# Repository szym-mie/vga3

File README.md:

# VGA FPGA Video Card implementation

## Display

This module works in standard VGA mode of 640x480 at 60Hz monitor refresh rate. The picture itself was scaled down to 160x120, but can be reverted to be true 640x480.

Full specification:

```
pixel clock: 25MHz
-0.7% deviation from ideal 25.175MHz

pixel mode: RGB222 6bpp
max analog color output voltage: 0.6V
sync signal level: 3.3V
```

## Hardware

### CAUTION

SPI connection requires 3.3V voltage level for safe operation

---

Apart from standard VGA connector, there is a SPI connection:

```
[  GND ]--(1)
< CSEL ]--(2)
< MOSI ]--(3)
< SCLK ]--(4)
```

FPGA:
```
MIMAS SPARTAN6 MODULE
```

Memory:
```
IS61LV5128AL 512K x 8 HIGH-SPEED CMOS STATIC RAM
access max time: 10, 12ns
full read/write max time: <20ns 
```

## Video memory

The video memory access is handled by module `vmmu.v`, which coordinates read access by VGA display unit and write access by SPI interface.

The basic working mechanism is the use of FIFOs to queue request addresses and read/write data.
Then the module can alternate between executing read and write requests, or if only one source has an active request, only that source is being processed.

The usage of FIFOs also make the system memory independent of other video circutry in terms of clock domains, further making the design more flexible.

## Schematics

As of recent update I've recovered KiCAD schematics and PCB design that contained system memory, SPI input and VGA connector. Those can be found under `kicad` directory.

## Modules

- spi.v - 8-bit SPI sampling receiver
- vbuf.v - video output buffer, also able to read 3 packed bytes to 4 pixels
- vcmd2v.v - video command processor, interacts with received data from SPI
- vctl.v - video output counter unit, sends signals related to video signal blanking and issues pixel read requests
- vsig.v - generates HSync and VSync VGA signals, along with global blank signal
- fifo.v - First-In-First-Out, asynchronous queue, with Full/Empty signals
- seqfifo.v - Generates sequences of addresses from staring address behaving as regular FIFO
- vmmu.v - video memory managment unit, time-slots reads and writes, controls memory chip
- vga.v - top-level module

## Bugs

#### 160x120 picture resolution (unresolved)

This was a hardware fault that prevented me from using a full 640x480. It turned out that one of the address lines was busted and it basically could corrupt the whole lower half of the screen. In theory I such issue could be remedied remap that region to an area that didn't use that address line.

#### PCB design mistake (fixed)

Due to confusing and just plain wrong schematic of pin headers that was published on Mimas site, one of data lines ended up connected to chip ground. This required an ad hoc jumper wire to be connected to a new location on a pin header, and a previous trace to be cut.

#### Dummy byte write needed after cursor move (unresolved)

An annoying issue, this results from tricky synchronization problems when the command to change cursor location is received. I was unable to fix it due to time constraint, instead a software workadround was devised, by writing a dummy byte just after `vga_set_xy`. This solution is not perfect and can cause flickering, depending on SPI data rate.

## Example driver code

A simple test driver code for ATMega88 (and its derivitives) can be found in `test_driver` directory. This test includes a simple color pallette pattern and animated analog speedometer.

The other example is included as a submodule [`vga_snake`](https://github.com/szym-mie/vga_snake) and it's a snake game demo written in C.

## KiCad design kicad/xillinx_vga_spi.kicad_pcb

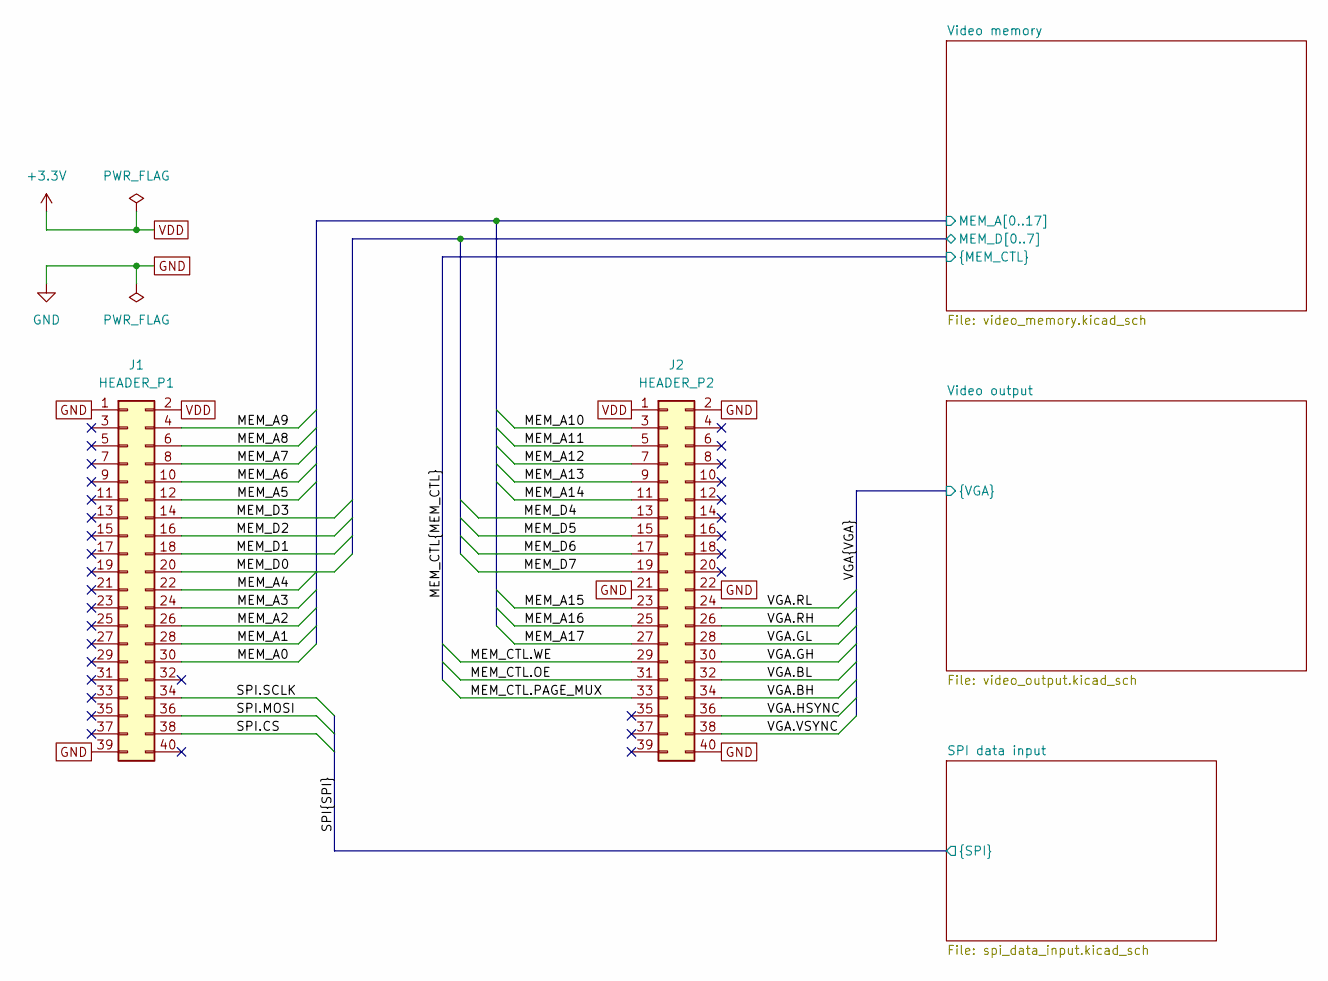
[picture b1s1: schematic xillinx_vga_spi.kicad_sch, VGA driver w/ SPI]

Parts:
J1: HEADER_P1; PinHeader_2x20_P2.54mm_Vertical
J2: HEADER_P2; PinHeader_2x20_P2.54mm_Vertical

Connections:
/MEM_CTL.OE: J2.31; also elsewhere on the board
/MEM_CTL.PAGE_MUX: J2.33; also elsewhere on the board
/MEM_CTL.WE: J2.29; also elsewhere on the board
/SPI.CS: J1.38; also elsewhere on the board
/SPI.MOSI: J1.36; also elsewhere on the board
/SPI.SCLK: J1.34; also elsewhere on the board
/VGA.BH: J2.34; also elsewhere on the board
/VGA.BL: J2.32; also elsewhere on the board
/VGA.GH: J2.30; also elsewhere on the board
/VGA.GL: J2.28; also elsewhere on the board
/VGA.HSYNC: J2.36; also elsewhere on the board
/VGA.RH: J2.26; also elsewhere on the board
/VGA.RL: J2.24; also elsewhere on the board
/VGA.VSYNC: J2.38; also elsewhere on the board
/Video memory/MEM_A0: J1.30; also elsewhere on the board
/Video memory/MEM_A1: J1.28; also elsewhere on the board
/Video memory/MEM_A2: J1.26; also elsewhere on the board
/Video memory/MEM_A3: J1.24; also elsewhere on the board
/Video memory/MEM_A4: J1.22; also elsewhere on the board
/Video memory/MEM_A5: J1.12; also elsewhere on the board
/Video memory/MEM_A6: J1.10; also elsewhere on the board
/Video memory/MEM_A7: J1.8; also elsewhere on the board
/Video memory/MEM_A8: J1.6; also elsewhere on the board
/Video memory/MEM_A9: J1.4; also elsewhere on the board
/Video memory/MEM_A10: J2.3; also elsewhere on the board
/Video memory/MEM_A11: J2.5; also elsewhere on the board
/Video memory/MEM_A12: J2.7; also elsewhere on the board
/Video memory/MEM_A13: J2.9; also elsewhere on the board
/Video memory/MEM_A14: J2.11; also elsewhere on the board
/Video memory/MEM_A15: J2.23; also elsewhere on the board
/Video memory/MEM_A16: J2.25; also elsewhere on the board
/Video memory/MEM_A17: J2.27; also elsewhere on the board
/Video memory/MEM_D0: J1.20; also elsewhere on the board
/Video memory/MEM_D1: J1.18; also elsewhere on the board
/Video memory/MEM_D2: J1.16; also elsewhere on the board
/Video memory/MEM_D3: J1.14; also elsewhere on the board
/Video memory/MEM_D4: J2.13; also elsewhere on the board
/Video memory/MEM_D5: J2.15; also elsewhere on the board
/Video memory/MEM_D6: J2.17; also elsewhere on the board
/Video memory/MEM_D7: J2.19; also elsewhere on the board
GND: J1.1, J1.39, J2.2, J2.21, J2.22, J2.40; also elsewhere on the board
VDD: J1.2, J2.1; also elsewhere on the board

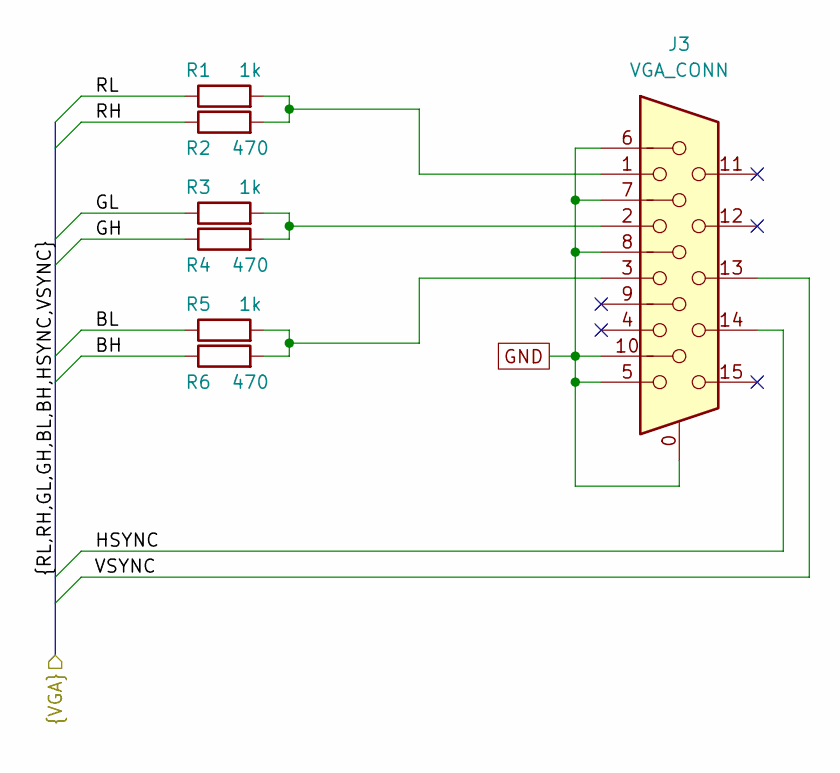
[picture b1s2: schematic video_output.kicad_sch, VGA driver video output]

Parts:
J3: VGA_CONN; L77HDE15SD1CH4FVGA
R1, R3, R5: 1k; R_0805_2012Metric_Pad1.20x1.40mm_HandSolder
R2, R4, R6: 470; R_0805_2012Metric_Pad1.20x1.40mm_HandSolder

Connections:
/VGA.BH: R6.1; also elsewhere on the board
/VGA.BL: R5.1; also elsewhere on the board
/VGA.GH: R4.1; also elsewhere on the board
/VGA.GL: R3.1; also elsewhere on the board
/VGA.HSYNC: J3.14; also elsewhere on the board
/VGA.RH: R2.1; also elsewhere on the board
/VGA.RL: R1.1; also elsewhere on the board
/VGA.VSYNC: J3.13; also elsewhere on the board
GND: J3.0, J3.5, J3.6, J3.7, J3.8, J3.10; also elsewhere on the board
unnamed: J3.1, R1.2, R2.2
unnamed: J3.2, R3.2, R4.2
unnamed: J3.3, R5.2, R6.2

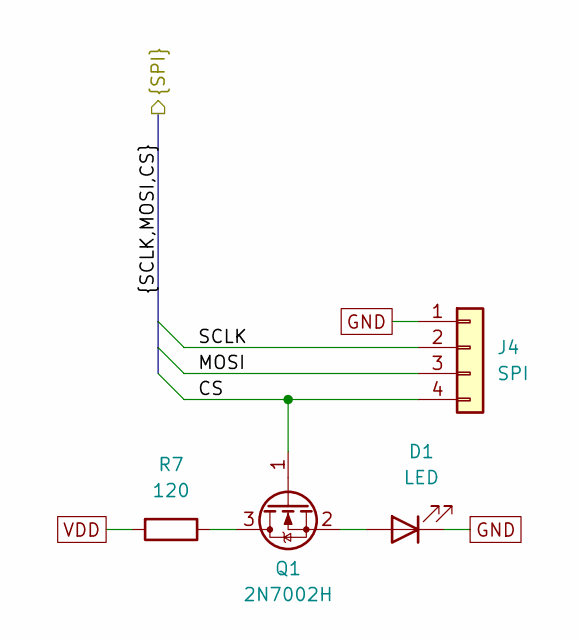
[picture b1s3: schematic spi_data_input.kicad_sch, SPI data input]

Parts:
D1: LED; LED_1206_3216Metric_Pad1.42x1.75mm_HandSolder
J4: SPI; PinSocket_1x04_P2.54mm_Horizontal
Q1: 2N7002H; SOT-23
R7: 120; R_0805_2012Metric_Pad1.20x1.40mm_HandSolder

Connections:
/SPI.CS: J4.4, Q1.1 (G); also elsewhere on the board
/SPI.MOSI: J4.3; also elsewhere on the board
/SPI.SCLK: J4.2; also elsewhere on the board
GND: D1.1 (K), J4.1; also elsewhere on the board
unnamed: D1.2 (A), Q1.2 (S)
unnamed: Q1.3 (D), R7.1
VDD: R7.2; also elsewhere on the board

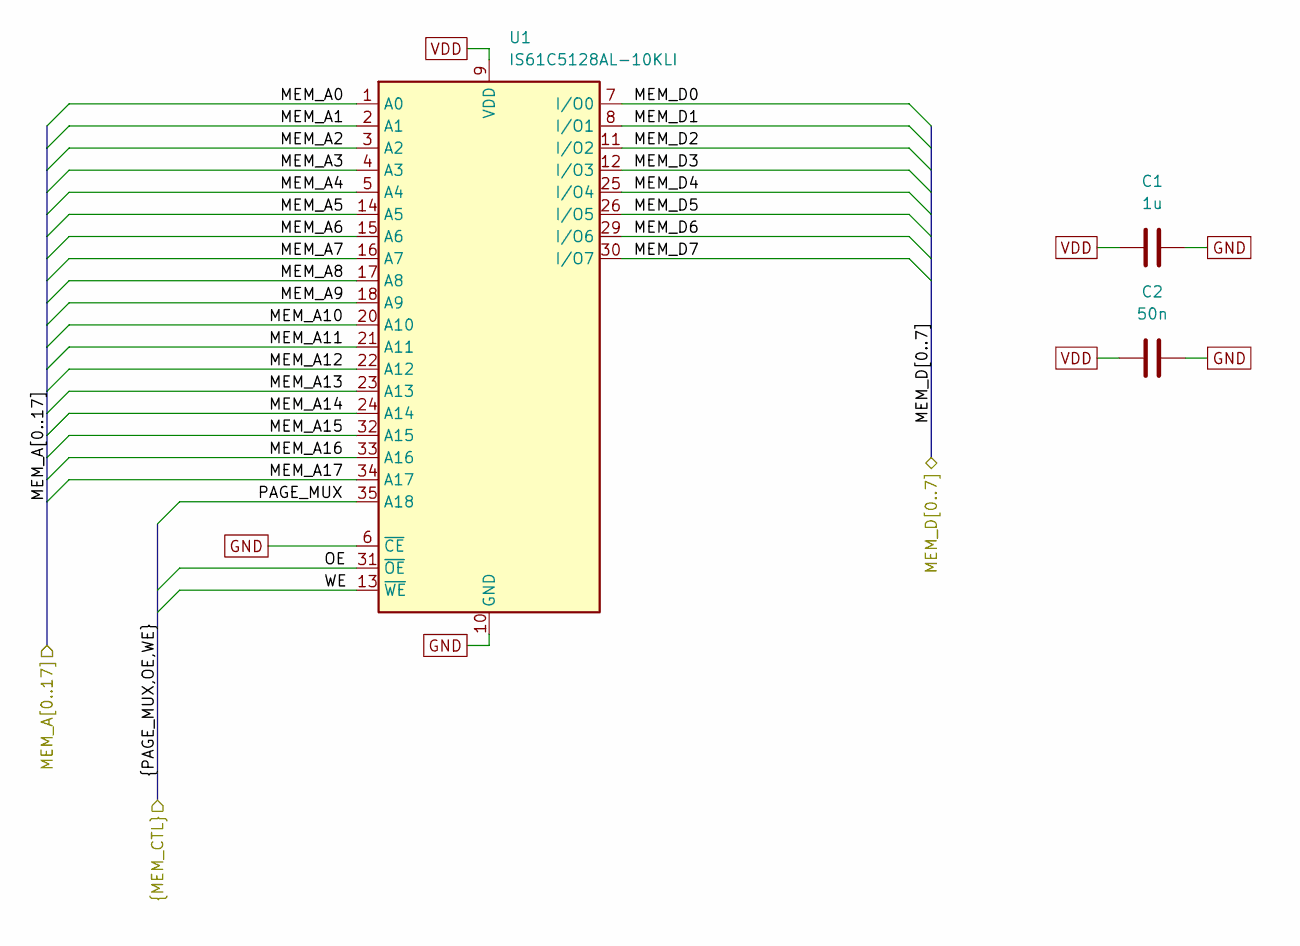
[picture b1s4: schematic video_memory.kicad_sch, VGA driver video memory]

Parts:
C1: 1u; C_0805_2012Metric_Pad1.18x1.45mm_HandSolder
C2: 50n; C_0805_2012Metric_Pad1.18x1.45mm_HandSolder
U1: IS61C5128AL-10KLI; SOJ-36_10.16x23.49mm_P1.27mm

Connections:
/MEM_CTL.OE: U1.31 (~OE); also elsewhere on the board
/MEM_CTL.PAGE_MUX: U1.35 (A18); also elsewhere on the board
/MEM_CTL.WE: U1.13 (~WE); also elsewhere on the board
/Video memory/MEM_A0: U1.1 (A0); also elsewhere on the board
/Video memory/MEM_A1: U1.2 (A1); also elsewhere on the board
/Video memory/MEM_A2: U1.3 (A2); also elsewhere on the board
/Video memory/MEM_A3: U1.4 (A3); also elsewhere on the board
/Video memory/MEM_A4: U1.5 (A4); also elsewhere on the board
/Video memory/MEM_A5: U1.14 (A5); also elsewhere on the board
/Video memory/MEM_A6: U1.15 (A6); also elsewhere on the board
/Video memory/MEM_A7: U1.16 (A7); also elsewhere on the board
/Video memory/MEM_A8: U1.17 (A8); also elsewhere on the board
/Video memory/MEM_A9: U1.18 (A9); also elsewhere on the board
/Video memory/MEM_A10: U1.20 (A10); also elsewhere on the board
/Video memory/MEM_A11: U1.21 (A11); also elsewhere on the board
/Video memory/MEM_A12: U1.22 (A12); also elsewhere on the board
/Video memory/MEM_A13: U1.23 (A13); also elsewhere on the board
/Video memory/MEM_A14: U1.24 (A14); also elsewhere on the board
/Video memory/MEM_A15: U1.32 (A15); also elsewhere on the board
/Video memory/MEM_A16: U1.33 (A16); also elsewhere on the board
/Video memory/MEM_A17: U1.34 (A17); also elsewhere on the board
/Video memory/MEM_D0: U1.7 (I/O0); also elsewhere on the board
/Video memory/MEM_D1: U1.8 (I/O1); also elsewhere on the board
/Video memory/MEM_D2: U1.11 (I/O2); also elsewhere on the board
/Video memory/MEM_D3: U1.12 (I/O3); also elsewhere on the board
/Video memory/MEM_D4: U1.25 (I/O4); also elsewhere on the board
/Video memory/MEM_D5: U1.26 (I/O5); also elsewhere on the board
/Video memory/MEM_D6: U1.29 (I/O6); also elsewhere on the board
/Video memory/MEM_D7: U1.30 (I/O7); also elsewhere on the board
GND: C1.2, C2.2, U1.6 (~CE), U1.10 (GND), U1.28 (GND); also elsewhere on the board
VDD: C1.1, C2.1, U1.9 (VDD), U1.27 (VDD); also elsewhere on the board

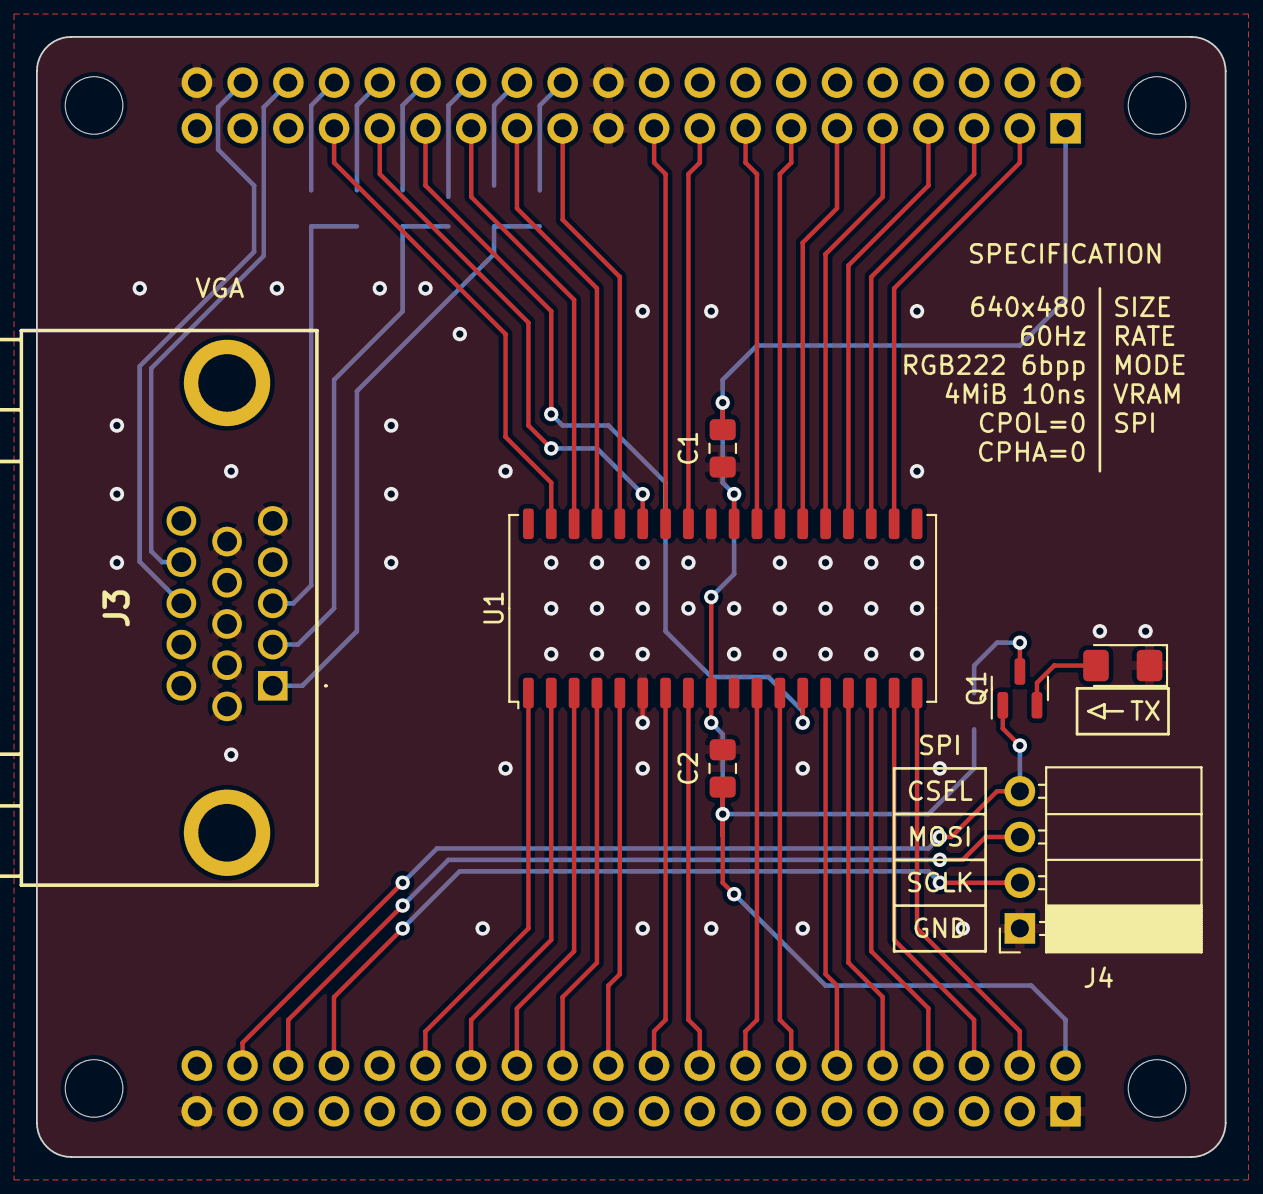
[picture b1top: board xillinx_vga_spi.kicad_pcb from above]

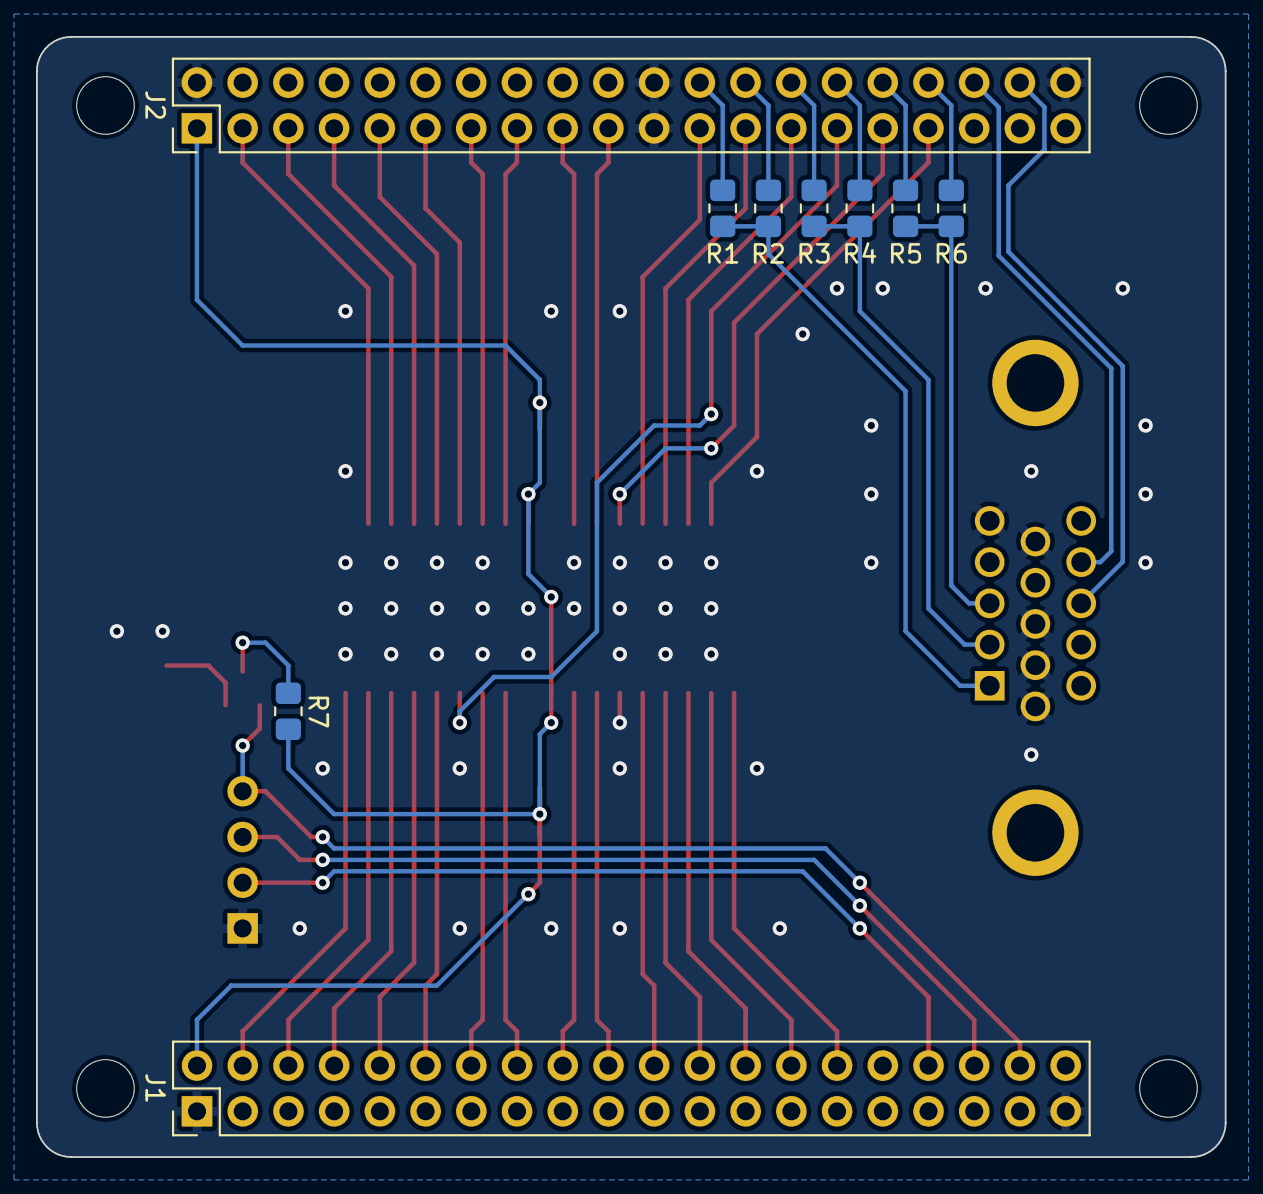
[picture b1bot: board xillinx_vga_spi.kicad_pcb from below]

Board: 2 copper layers, 66.0 x 62.2 mm, 16 parts (9 on the bottom side), 47 nets.

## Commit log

2024-05-06 Add source files
2024-05-06 Add LICENSE
2024-05-07 Fix common errors in synthesis and translation for Spartan 6
2024-05-07 Add graphs, small timing fixes
2024-10-14 Upload schematics, late noon README
2024-10-14 Fix the README
2024-10-14 Late afternoon driver code upload and README update
2025-03-28 Added vga_snake submodule
